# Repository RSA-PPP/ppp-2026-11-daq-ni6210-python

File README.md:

# ppp-2026-12-daq-ni6210-python

> **Red Sísmica del Austro (RSA) — Universidad de Cuenca**  
> Prácticas Preprofesionales (PPP) • Instrumentación Virtual, Procesamiento Digital de Señales y Metrología

---

## 📋 Ficha Técnica del Proyecto

| Campo | Detalle |
| :--- | :--- |
| **Código Institucional** | `RSA-PPP-2026-12` |
| **Nombre del Proyecto** | Sistema de Adquisición, Calibración y Caracterización Metrológica de Sensores Geotécnicos en Python (NI USB-6210) |
| **Pasante** | Christopher Carchipulla (`christopher.carchipulla@ucuenca.edu.ec`) |
| **Carrera / Institución** | Ingeniería en Telecomunicaciones — Universidad de Cuenca |
| **Tutor Institucional** | Ing. Milton Muñoz (`milton.munozc@ucuenca.edu.ec`) — RSA |
| **Duración / Horas** | 144 horas (10.5 semanas) • Presencial |
| **Fecha de Ejecución** | 2026-10-01 al 2026-12-18 |
| **Estado** | `En Ejecución` |

---

## 🎯 Descripción General y Objetivos

La Red Sísmica del Austro (RSA) dispone de instrumental geotécnico para la supervisión de deformaciones milimétricas y desplazamientos relativos en presas hidroeléctricas. Este proyecto implementa una suite de instrumentación virtual completa y trazable en **Python 3.10+** gobernando una tarjeta de adquisición de datos **National Instruments NI USB-6210** (16 entradas analógicas, resolución de 16 bits hasta 250 kSPS).

El sistema digitaliza simultáneamente **16 transductores geotécnicos**:
* **2 canales para Puentes de Wheatstone:** Destinados a galgas extensométricas de deformación estructural, con acondicionamiento analógico de ultra bajo ruido mediante amplificadores de instrumentación **INA114AP**.
* **14 canales para sensores potenciométricos:** Destinados a transductores lineales de desplazamiento relativo (vástago/hilo).

La solución desacopla la configuración de los transductores mediante archivos estructurados (`YAML`/`JSON`), aplica equilibrado y cero eléctrico de software (tara dinámica), ejecuta filtrado digital en tiempo real contra ruido de red industrial (60 Hz), genera persistencia dual en CSV/Parquet y ofrece un panel de supervisión gráfica continuo y reactivo en **PyQtGraph**.

### Objetivos Clave
1. **Auditoría de Hardware y Entorno NI-DAQmx:** Validar circuitalmente las ganancias de los amplificadores INA114AP, verificar límites de tensión ($\pm 10\text{ V}$) y configurar el entorno de ejecución en Python con el driver oficial `nidaqmx`.
2. **Arquitectura de Software y Configuración Desacoplada:** Diseñar una arquitectura orientada a objetos modular gobernada por un archivo de configuración externo (`sensors_config.yaml`) para asignar canales, modos de conexión (RSE/NRSE/Diferencial) y parámetros de calibración.
3. **Módulo de Procesamiento para Puentes de Wheatstone:** Implementar equilibrado eléctrico, ajuste dinámico de cero y conversión analítica de microvoltios a microdeformación ($\mu\varepsilon$) con validación por resistencias patrón.
4. **Módulo de Calibración de Desplazamiento Potenciométrico:** Implementar el muestreo síncrono de los 14 canales, evaluando diafonía (*cross-talk*) y ejecutando regresiones lineales metrológicas en banco micrométrico.
5. **Filtrado Digital y Persistencia Segura:** Diseñar filtros digitales pasabajas Butterworth (10 Hz) contra armónicos de 60 Hz, supervisión proactiva de anomalías (saturación y desconexión) y almacenamiento sincronizado en CSV con logs de diagnóstico.
6. **Interfaz Gráfica en Tiempo Real y Ensayo de Estrés:** Desarrollar un panel reactivo en `PyQtGraph` desacoplado del hilo de muestreo y validar la estabilidad en una prueba continua ininterrumpida de 24 a 48 horas.
7. **Documentación Metrológica e Informe Final:** Elaborar manuales de calibración metrológica, guía de troubleshooting e Informe Técnico Final.

> 📄 Para consultar el cronograma detallado semana a semana, la carga horaria y los checkpoints verificables, revisa el [Plan de Trabajo Oficial](docs/planificacion.md).

---

## 🏗️ Arquitectura del Sistema y Flujo de Trabajo

```text
+-----------------------------------------------------------------------------------+
|                        DIAGRAMA DE ARQUITECTURA DEL SISTEMA                       |
+-----------------------------------------------------------------------------------+
|                                                                                   |
|  [Sensores Geotécnicos en Presa]                                                  |
|  ├── 2x Puentes de Wheatstone (Galgas) ---> [Amplificadores INA114AP]            |
|  └── 14x Potenciómetros de Desplazamiento -> [Divisores / Acondicionamiento]      |
|                                                     |                             |
|                                                     v                             |
|                                        [NI USB-6210 DAQ Hardware]                 |
|                                        (16 AI, 16 bits, hasta 250 kSPS)           |
|                                                     |                             |
|                                                     v (USB Bus / NI-DAQmx Driver) |
|  [Software DAQ en Python 3.10+]                     |                             |
|  ├── DeviceManager & ConfigLoader (YAML) <----------+                             |
|  ├── DataEngine (Buffers circulares & Callbacks)                                  |
|  ├── Filtros Digitales Butterworth (fc=10 Hz) & Rutinas de Tara                   |
|  ├── Conversión Metrológica (uε y mm) & Detección de Fallos / Saturación          |
|  └── Persistencia Dual: raw_voltages.csv + engineering_data.csv                   |
|                                                     |                             |
|                                                     v                             |
|  [Interfaz Gráfica en Tiempo Real - PyQtGraph] <----+                             |
|  ├── Cuadrícula de 16 canales con barras de nivel y semáforos de alarma           |
|  └── Osciloscopio multicanal para inspección de tendencias dinámicas              |
+-----------------------------------------------------------------------------------+
```

---

## 📂 Estructura del Repositorio

> [!IMPORTANT]
> **Estructura Raíz Inmutable:** Para mantener la coherencia con los lineamientos institucionales de la RSA, la estructura de carpetas raíz no debe ser alterada ni renombrada sin previa coordinación con el tutor.

```text
ppp-2026-12-daq-ni6210-python/
├── data/
│   ├── evidence/              # Gráficas de calibración, capturas de osciloscopio y logs
│   └── raw_samples/           # Volcados de datos brutos (.csv de prueba, series temporales)
│
├── docs/
│   ├── hardware/              # Esquemáticos del acondicionador, memorias de cálculo INA114AP
│   ├── troubleshooting/       # Bitácora de problemas técnicos, ruidos y soluciones
│   └── planificacion.md       # Documento rector del plan de trabajo (144h) y checkpoints
│
├── software/
│   ├── common/                # Constantes, enumeraciones y estructuras de datos compartidas
│   ├── drivers/               # Envoltorios de bajo nivel para NI-DAQmx
│   ├── daq_core/              # Motor de adquisición, DeviceManager, ConfigLoader y filtros
│   └── tests/                 # Scripts de prueba unitaria, benchmarks y simulación
│
├── python/
│   ├── scripts/               # Scripts de ejecución rápida, calibración y exportación
│   ├── utils/                 # Funciones auxiliares matemáticas, de log y persistencia
│   └── requirements.txt       # Dependencias de software en Python
│
├── README.md                  # Este documento
└── .gitignore                 # Exclusiones de Git
```

---

## 🛠️ Herramientas y Requisitos de Desarrollo

* **Hardware / Instrumental:**
  - Tarjeta de Adquisición de Datos National Instruments **NI USB-6210**.
  - Tarjeta de Acondicionamiento Analógico con amplificadores Burr-Brown / TI **INA114AP**.
  - Multímetro digital de banco de 6.5 dígitos y caja de décadas de resistencias patrón (precisión $\pm 0.05\%$).
  - Banco de desplazamiento micrométrico con micrómetro digital de precisión.
* **Controladores y Drivers:**
  - Controlador oficial **NI-DAQmx** instalado en el sistema operativo.
* **Entorno de Programación:**
  - Python 3.10+ en entorno virtual (`.venv`).
  - Dependencias listadas en `python/requirements.txt`:
    ```bash
    pip install -r python/requirements.txt
    ```

---

## 🚀 Puesta en Marcha

### 1. Clonar el Repositorio
```bash
git clone git@github.com-rsa:RSA-PPP/ppp-2026-12-daq-ni6210-python.git
cd ppp-2026-12-daq-ni6210-python
```

### 2. Configuración del Entorno Virtual de Python
```powershell
python -m venv .venv
.\.venv\Scripts\Activate.ps1
pip install --upgrade pip
pip install -r python/requirements.txt
```

### 3. Verificación del Hardware DAQ
Ejecutar el diagnóstico rápido para comprobar la detección de la tarjeta NI USB-6210:
```powershell
python -c "import nidaqmx.system; print(nidaqmx.system.System.local().devices)"
```

---

## 🛡️ Reglas de Trabajo y Control de Versiones

Para asegurar la calidad y trazabilidad del proyecto durante las prácticas:

1. **Rama Principal:** La rama activa de trabajo es **`main`**. Realiza commits frecuentes y atómicos al finalizar cada bloque o jornada de trabajo.
2. **Formato de Commits:** Utiliza la convención estándar en minúsculas:
   - `feat: [nueva funcionalidad, clase o módulo de adquisición implementado]`
   - `fix: [corrección de bug en cálculo, filtrado, calibración o script]`
   - `docs: [actualización de documentación técnica, esquemas o bitácora]`
   - `test: [incorporación o ejecución de pruebas de estrés y calibración]`
   - `refactor: [optimización de código sin cambio de comportamiento]`
3. **Integridad de Datos:** No subas archivos temporales pesados de pruebas o series temporales masivas sin comprimir. Apóyate en las reglas definidas en `.gitignore`.

---

## 📞 Contacto y Soporte Institucional

* **Tutor Institucional:** Ing. Milton Muñoz (`milton.munozc@ucuenca.edu.ec`)
* **Institución:** [Red Sísmica del Austro (RSA)](https://redsismicaaustro.github.io/RSA-Metodologias) — Universidad de Cuenca

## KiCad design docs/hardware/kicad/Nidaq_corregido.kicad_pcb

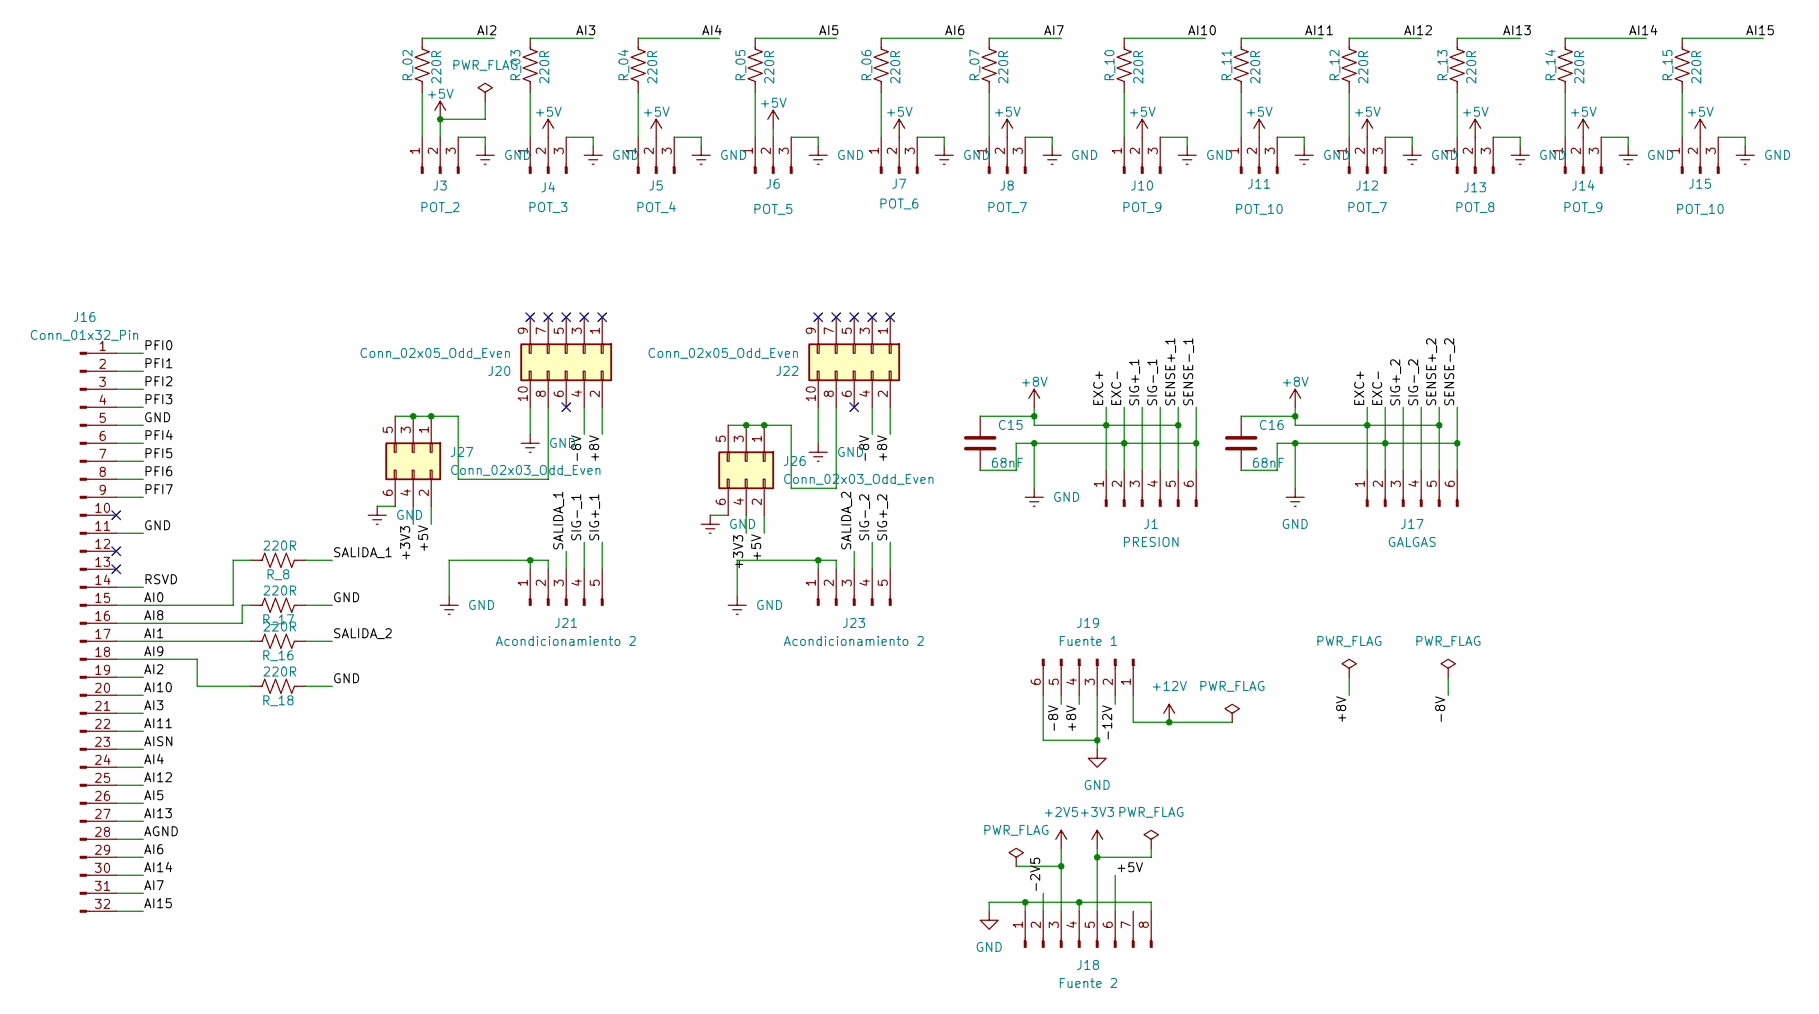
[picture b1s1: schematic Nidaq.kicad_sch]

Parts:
C15, C16: 68nF; C_Disc_D5.0mm_W2.5mm_P5.00mm
J1: PRESION; JST_EH_B6B-EH-A_1x06_P2.50mm_Vertical
J3: POT_2; JST_EH_B3B-EH-A_1x03_P2.50mm_Vertical
J4: POT_3; JST_EH_B3B-EH-A_1x03_P2.50mm_Vertical
J5: POT_4; JST_EH_B3B-EH-A_1x03_P2.50mm_Vertical
J6: POT_5; JST_EH_B3B-EH-A_1x03_P2.50mm_Vertical
J7: POT_6; JST_EH_B3B-EH-A_1x03_P2.50mm_Vertical
J8, J12: POT_7; JST_EH_B3B-EH-A_1x03_P2.50mm_Vertical
J10, J14: POT_9; JST_EH_B3B-EH-A_1x03_P2.50mm_Vertical
J11, J15: POT_10; JST_EH_B3B-EH-A_1x03_P2.50mm_Vertical
J13: POT_8; JST_EH_B3B-EH-A_1x03_P2.50mm_Vertical
J16: Conn_01x32_Pin; NIDAQ USB 62XX
J17: GALGAS; JST_EH_B6B-EH-A_1x06_P2.50mm_Vertical
J18: Fuente 2; PinHeader_1x08_P2.54mm_Vertical
J19: Fuente 1; PinHeader_1x06_P2.54mm_Vertical
J20, J22: Conn_02x05_Odd_Even; PinHeader_2x05_P2.54mm_Vertical
J21, J23: Acondicionamiento 2; PinHeader_1x05_P2.54mm_Vertical
J26, J27: Conn_02x03_Odd_Even; PinHeader_2x03_P2.54mm_Vertical
R_02, R_03, R_04, R_05, R_06, R_07, R_8, R_10, R_11, R_12, R_13, R_14, R_15, R_16, R_17, R_18: 220R; R_Axial_DIN0207_L6.3mm_D2.5mm_P10.16mm_Horizontal

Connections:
+2V5: J18.3
+3V3: J18.5, J26.4, J27.4
+5V: J3.2, J4.2, J5.2, J6.2, J7.2, J8.2, J10.2, J11.2, J12.2, J13.2, J14.2, J15.2, J18.6, J26.2, J27.2
+8V: C15.2, C16.2, J1.1, J1.5, J17.1, J17.5, J19.4, J20.2, J22.2
+12V: J19.1
/-2V5: J18.2
/-8V: J19.5, J20.4, J22.4
/-12V: J19.2
/AGND: J16.28
/AI0: J16.15, R_8.2
/AI1: J16.17, R_16.2
/AI2: J16.19, R_02.2
/AI3: J16.21, R_03.2
/AI4: J16.24, R_04.2
/AI5: J16.26, R_05.2
/AI6: J16.29, R_06.2
/AI7: J16.31, R_07.2
/AI8: J16.16, R_17.2
/AI9: J16.18, R_18.2
/AI10: J16.20, R_10.2
/AI11: J16.22, R_11.2
/AI12: J16.25, R_12.2
/AI13: J16.27, R_13.2
/AI14: J16.30, R_14.2
/AI15: J16.32, R_15.2
/AISN: J16.23
/PFI0: J16.1
/PFI1: J16.2
/PFI2: J16.3
/PFI3: J16.4
/PFI4: J16.6
/PFI5: J16.7
/PFI6: J16.8
/PFI7: J16.9
/RSVD: J16.14
/SALIDA_1: J21.3, R_8.1
/SALIDA_2: J23.3, R_16.1
/SIG+_1: J1.3, J21.5
/SIG+_2: J17.3, J23.5
/SIG-_1: J1.4, J21.4
/SIG-_2: J17.4, J23.4
GND: C15.1, C16.1, J1.2, J1.6, J3.3, J4.3, J5.3, J6.3, J7.3, J8.3, J10.3, J11.3, J12.3, J13.3, J14.3, J15.3, J16.5, J16.11, J17.2, J17.6, J18.1, J18.4, J18.8, J19.3, J19.6, J20.10, J21.1, J21.2, J22.10, J23.1, J23.2, J26.6, J27.6, R_17.1, R_18.1
unnamed: J3.1, R_02.1
unnamed: J4.1, R_03.1
unnamed: J5.1, R_04.1
unnamed: J6.1, R_05.1
unnamed: J7.1, R_06.1
unnamed: J8.1, R_07.1
unnamed: J10.1, R_10.1
unnamed: J11.1, R_11.1
unnamed: J12.1, R_12.1
unnamed: J13.1, R_13.1
unnamed: J14.1, R_14.1
unnamed: J15.1, R_15.1
unnamed: J20.8, J27.1, J27.3, J27.5
unnamed: J22.8, J26.1, J26.3, J26.5

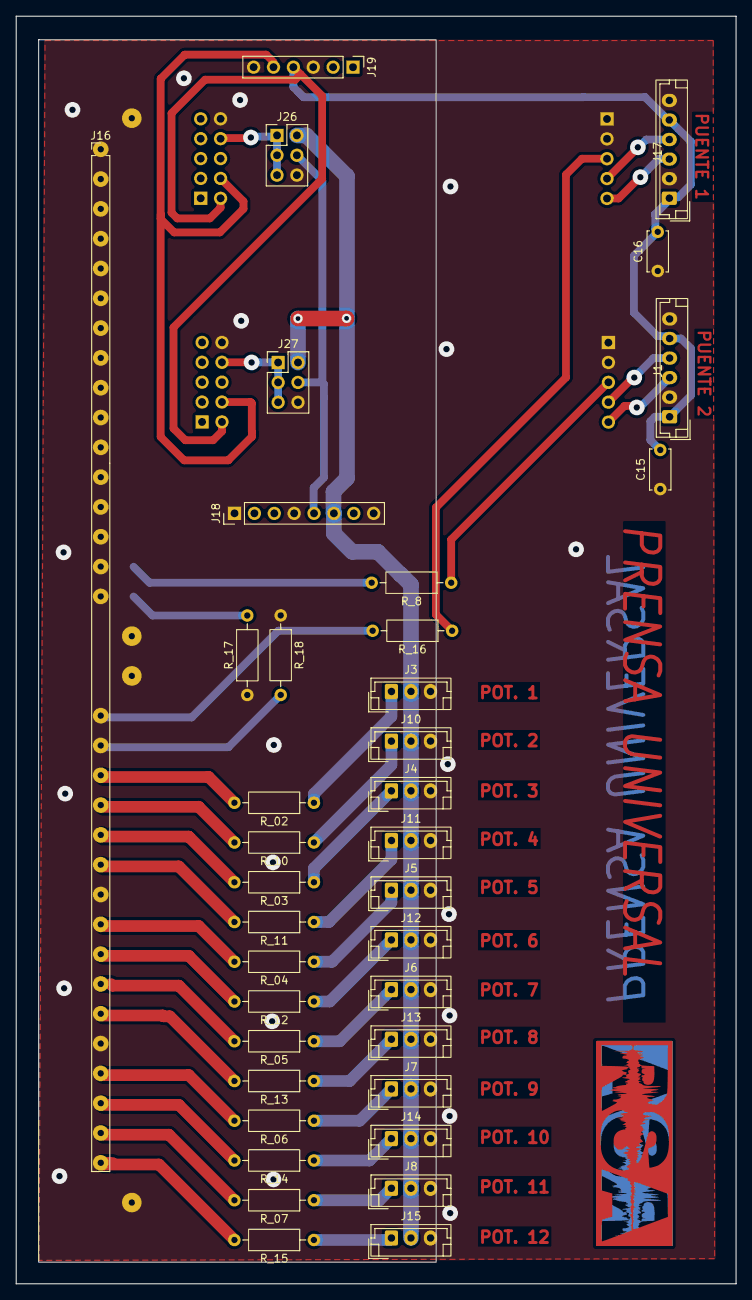
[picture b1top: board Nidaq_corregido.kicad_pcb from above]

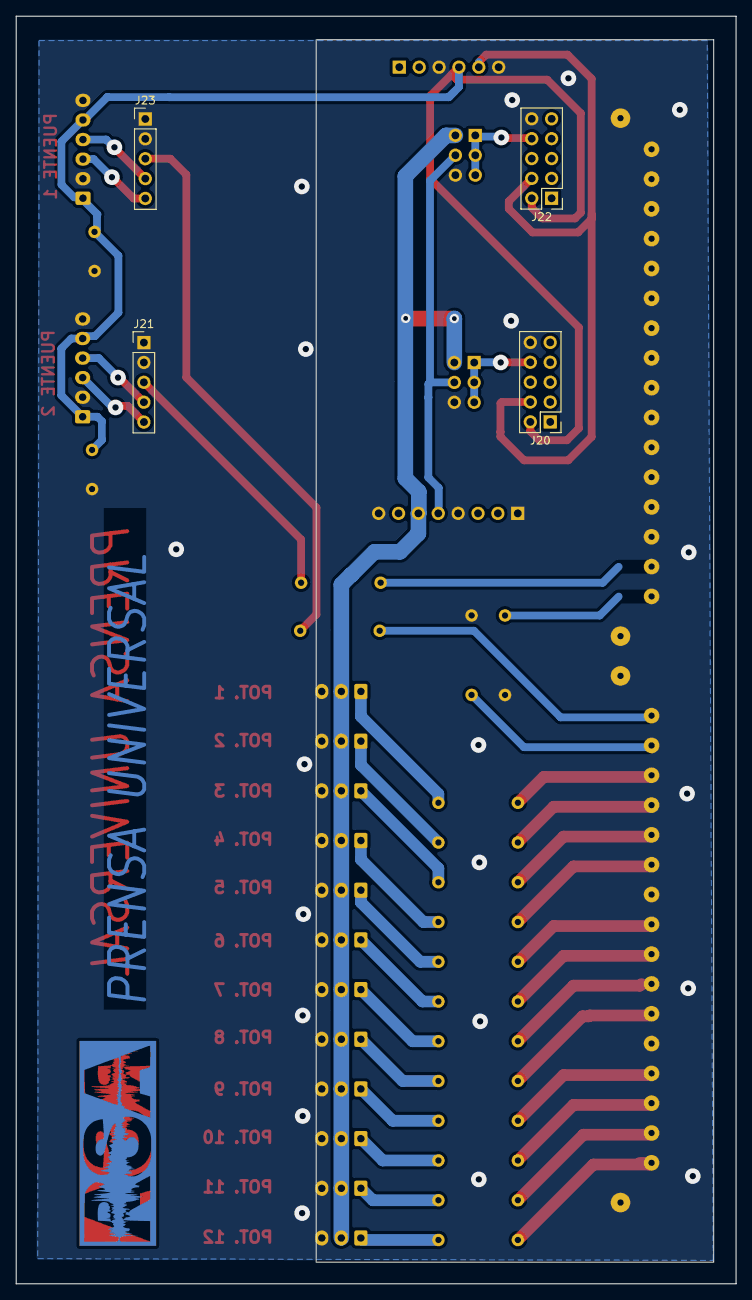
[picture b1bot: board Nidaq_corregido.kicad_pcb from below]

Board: 2 copper layers, 92.0 x 162.0 mm, 41 parts (4 on the bottom side), 41 nets.

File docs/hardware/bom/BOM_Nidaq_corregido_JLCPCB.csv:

Comment,Designator,Footprint,LCSC Part #
220R,"R_02,R_03,R_04,R_05,R_06,R_07,R_10,R_11,R_12,R_13,R_14,R_15,R_16,R_17,R_18,R_8",R_Axial_DIN0207_L6.3mm_D2.5mm_P10.16mm_Horizontal,
68nF,"C15,C16",C_Disc_D5.0mm_W2.5mm_P5.00mm,
Acondicionamiento 2,"J21,J23",PinHeader_1x05_P2.54mm_Vertical,
Conn_01x03_Pin,J,,
Conn_01x32_Pin,J16,NIDAQ  USB 62XX,
Conn_02x03_Odd_Even,"J26,J27",PinHeader_2x03_P2.54mm_Vertical,
Conn_02x05_Odd_Even,"J20,J22",PinHeader_2x05_P2.54mm_Vertical,
Fuente 1,J19,PinHeader_1x06_P2.54mm_Vertical,
Fuente 2,J18,PinHeader_1x08_P2.54mm_Vertical,
GALGAS,J17,JST_EH_B6B-EH-A_1x06_P2.50mm_Vertical,
POT_10,"J11,J15",JST_EH_B3B-EH-A_1x03_P2.50mm_Vertical,
POT_2,J3,JST_EH_B3B-EH-A_1x03_P2.50mm_Vertical,
POT_3,J4,JST_EH_B3B-EH-A_1x03_P2.50mm_Vertical,
POT_4,J5,JST_EH_B3B-EH-A_1x03_P2.50mm_Vertical,
POT_5,J6,JST_EH_B3B-EH-A_1x03_P2.50mm_Vertical,
POT_6,J7,JST_EH_B3B-EH-A_1x03_P2.50mm_Vertical,
POT_7,"J12,J8",JST_EH_B3B-EH-A_1x03_P2.50mm_Vertical,
POT_8,J13,JST_EH_B3B-EH-A_1x03_P2.50mm_Vertical,
POT_9,"J10,J14",JST_EH_B3B-EH-A_1x03_P2.50mm_Vertical,
PRESION,J1,JST_EH_B6B-EH-A_1x06_P2.50mm_Vertical,
